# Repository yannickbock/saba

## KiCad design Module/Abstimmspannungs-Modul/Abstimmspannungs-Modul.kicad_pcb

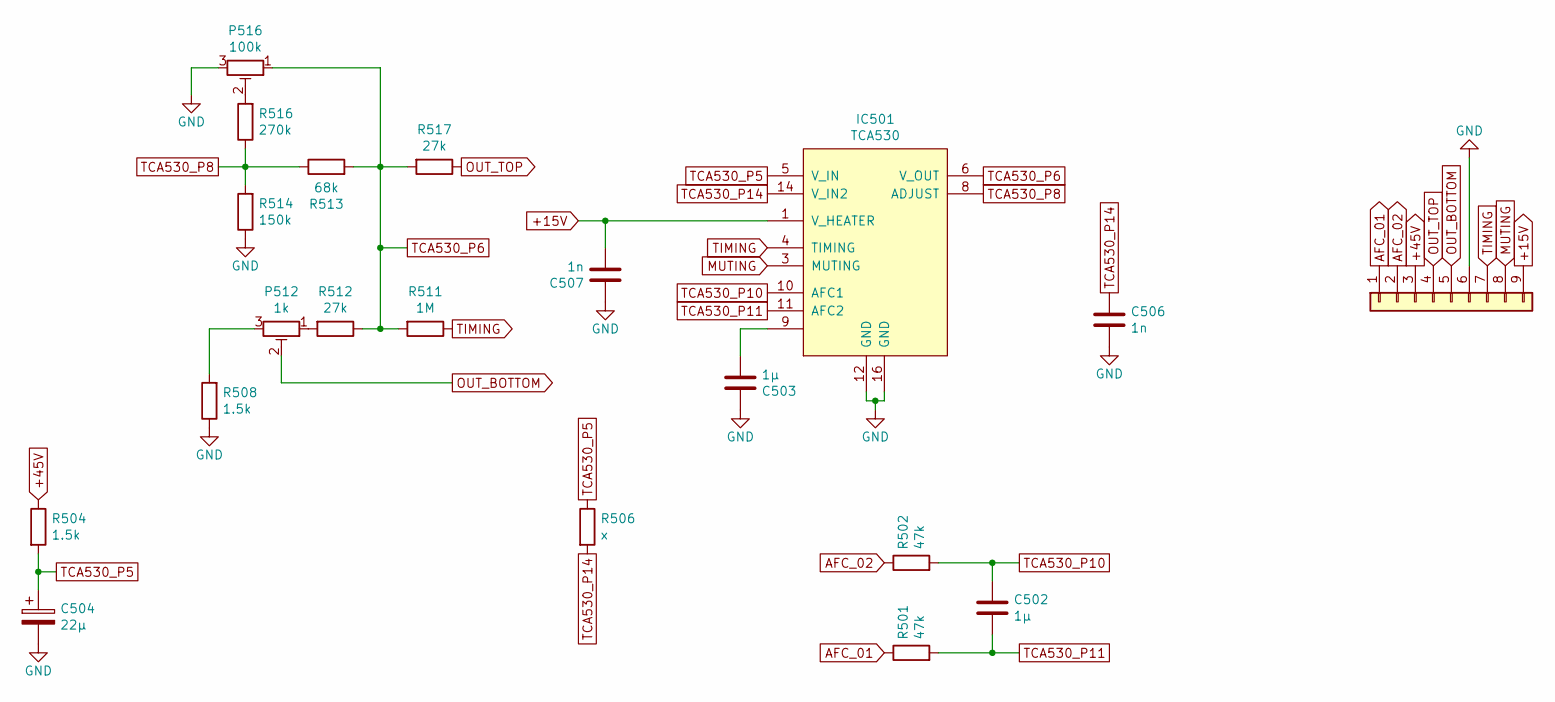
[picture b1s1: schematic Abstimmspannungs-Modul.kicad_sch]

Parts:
C502, C503: 1µ; C_Rect_L4.6mm_W5.5mm_P2.50mm_MKS02_FKP02
C504: 22µ; CP_Radial_D5.0mm_P2.00mm
C506, C507: 1n; C_Disc_D4.3mm_W1.9mm_P5.00mm
IC501: TCA530; DIP-16_W7.62mm
J1: Conn_01x09; Connector_01x09_5mm
P512: 1k; Potentiometer_Piher_PT-15-H05_Horizontal
P516: 100k; Potentiometer_Piher_PT-15-H05_Horizontal
R501, R502: 47k; R_Axial_DIN0207_L6.3mm_D2.5mm_P10.16mm_Horizontal
R504, R508: 1.5k; R_Axial_DIN0207_L6.3mm_D2.5mm_P10.16mm_Horizontal
R506: x; R_Axial_DIN0207_L6.3mm_D2.5mm_P10.16mm_Horizontal
R511: 1M; R_Axial_DIN0207_L6.3mm_D2.5mm_P10.16mm_Horizontal
R512, R517: 27k; R_Axial_DIN0207_L6.3mm_D2.5mm_P10.16mm_Horizontal
R513: 68k; R_Axial_DIN0207_L6.3mm_D2.5mm_P10.16mm_Horizontal
R514: 150k; R_Axial_DIN0207_L6.3mm_D2.5mm_P10.16mm_Horizontal
R516: 270k; R_Axial_DIN0207_L6.3mm_D2.5mm_P10.16mm_Horizontal

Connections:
+15V: C507.1, IC501.1 (V_HEATER), J1.9
+45V: J1.3, R504.1
AFC_01: J1.1, R501.1
AFC_02: J1.2, R502.1
GND: C503.2, C504.2, C506.1, C507.2, IC501.12 (GND), IC501.16 (GND), J1.6, P516.3, R508.1, R514.1
MUTING: IC501.3 (MUTING), J1.8
unnamed: C503.1, IC501.9
unnamed: P512.1, R512.2
unnamed: P512.3, R508.2
unnamed: P516.2, R516.2
OUT_BOTTOM: J1.5, P512.2
OUT_TOP: J1.4, R517.1
TCA530_P5: C504.1, IC501.5 (V_IN), R504.2, R506.1
TCA530_P6: IC501.6 (V_OUT), P516.1, R511.2, R512.1, R513.2, R517.2
TCA530_P8: IC501.8 (ADJUST), R513.1, R514.2, R516.1
TCA530_P10: C502.2, IC501.10 (AFC1), R502.2
TCA530_P11: C502.1, IC501.11 (AFC2), R501.2
TCA530_P14: C506.2, IC501.14 (V_IN2), R506.2
TIMING: IC501.4 (TIMING), J1.7, R511.1

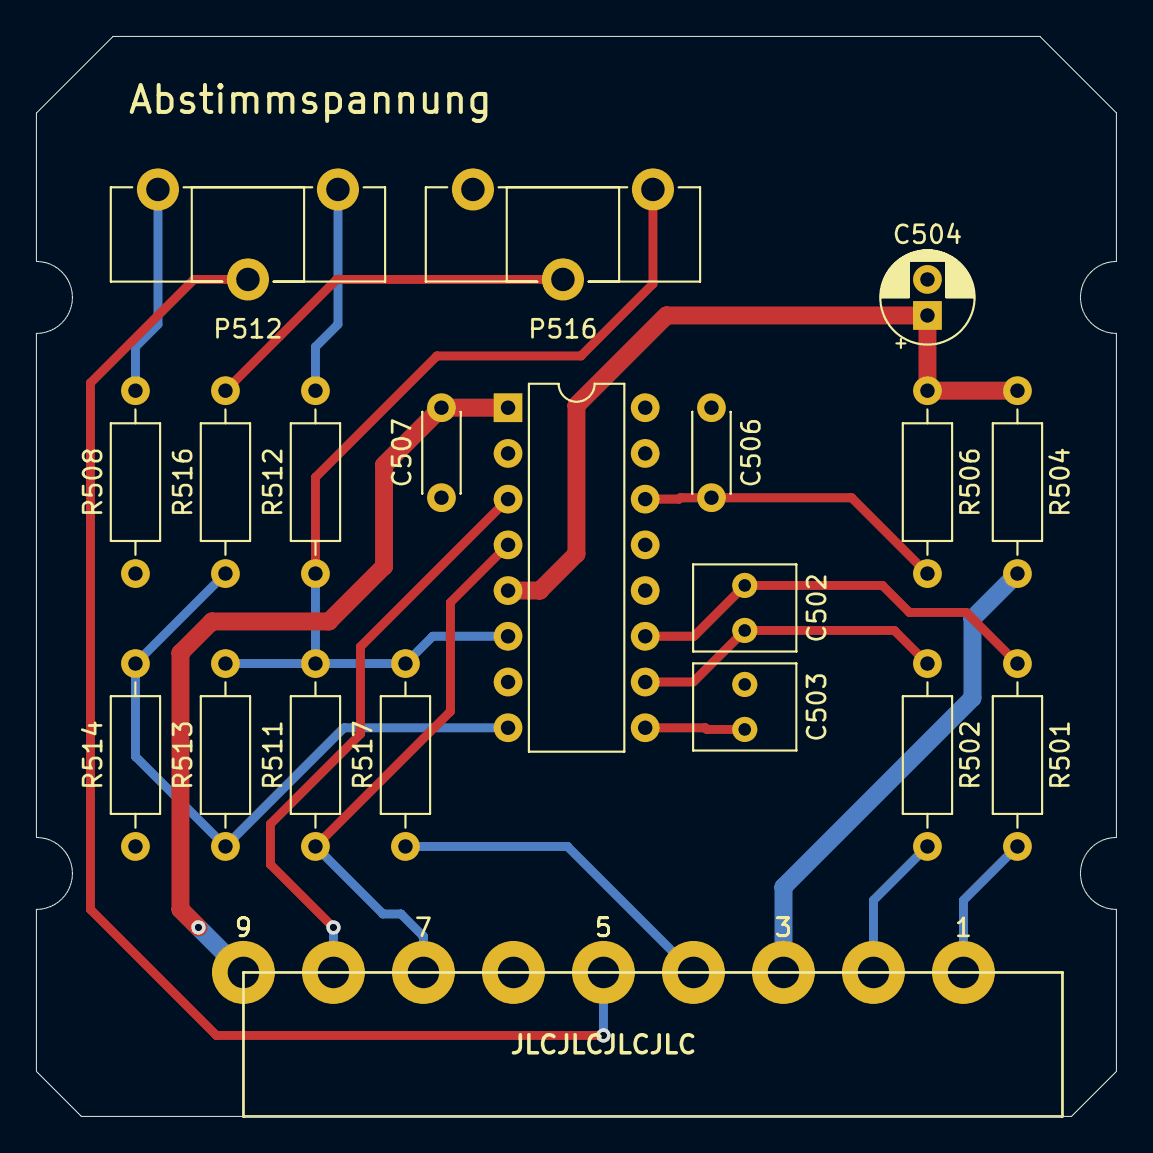
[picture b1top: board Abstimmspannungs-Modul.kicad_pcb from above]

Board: 2 copper layers, 60.0 x 60.0 mm, 20 parts (0 on the bottom side), 19 nets.

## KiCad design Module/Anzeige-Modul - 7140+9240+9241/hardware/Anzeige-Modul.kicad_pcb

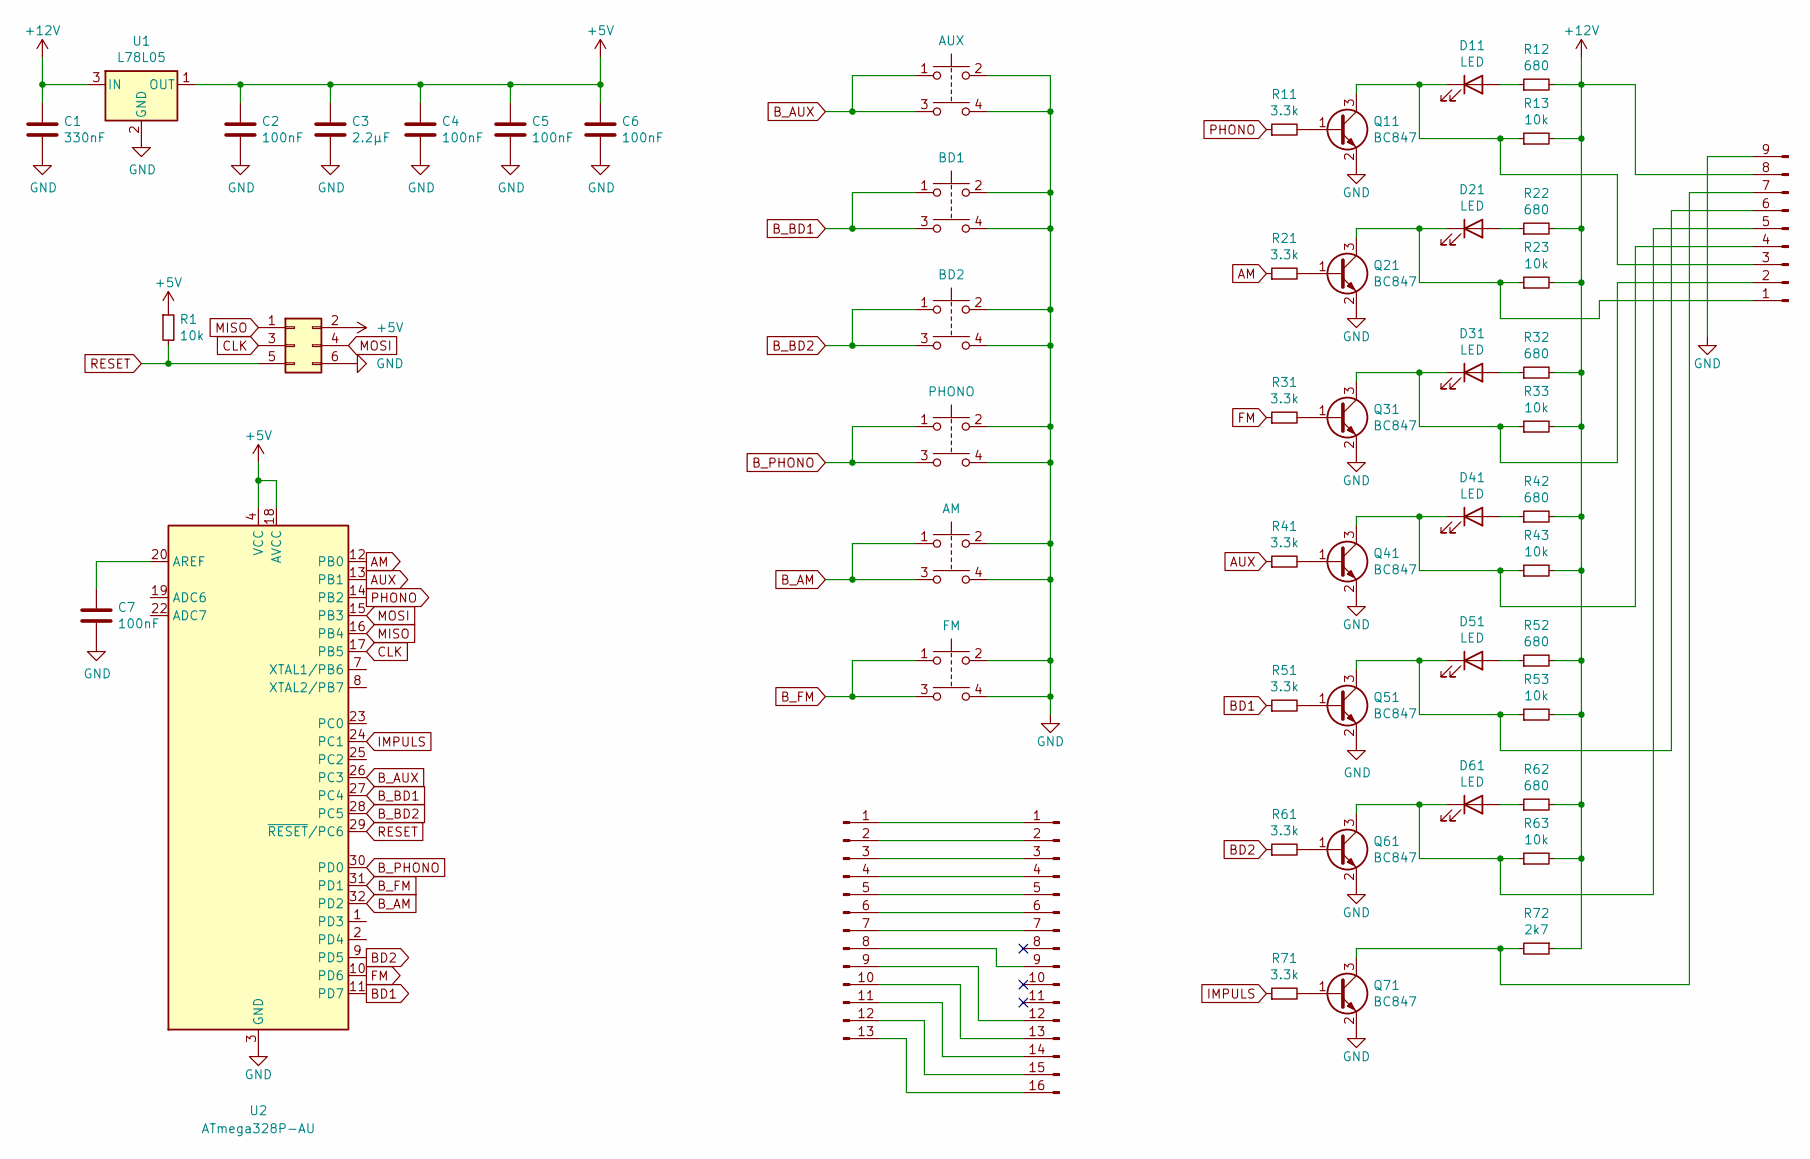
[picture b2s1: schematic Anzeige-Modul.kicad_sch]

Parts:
C1: 330nF; C_0805_2012Metric; LCSC C1740
C2, C4, C5, C6, C7: 100nF; C_0805_2012Metric; LCSC C49678
C3: 2.2µF; C_0805_2012Metric; LCSC C49217
D11, D21, D31, D41, D51, D61: LED; LED_Rectangular_W5.0mm_H2.0mm
J1: Conn_01x09_Male; PadArray_3.81mm_01x09
J3: Conn_02x03_Counter_Clockwise; PinHeader_2x03_P2.54mm_Vertical
J5: Conn_01x13_Male; PadArray_2.54mm_01x13
J6: Conn_01x16_Male; Pad_Array_2,54mm_16
Q11, Q21, Q31, Q41, Q51, Q61, Q71: BC847; SOT-23; LCSC C2146
R1, R13, R23, R33, R43, R53, R63: 10k; R_0805_2012Metric; LCSC C17414
R11, R21, R31, R41, R51, R61, R71: 3.3k; R_0805_2012Metric; LCSC C26010
R12, R22, R32, R42, R52: 680; R_0805_2012Metric; LCSC C17798
R62: 680; R_0805; LCSC C17798
R72: 2k7; R_0805_2012Metric; LCSC C17530
SW1: AUX; SW_PUSH_DPDT
SW2: BD1; SW_PUSH_DPDT
SW3: BD2; SW_PUSH_DPDT
SW4: PHONO; SW_PUSH_DPDT
SW5: AM; SW_PUSH_DPDT
SW6: FM; SW_PUSH_DPDT
U1: L78L05; SOT-89-3; LCSC C71136
U2: ATmega328P-AU; TQFP-32_7x7mm_P0.8mm; LCSC C14877

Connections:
+5V: C2.2, C3.2, C4.2, C5.2, C6.2, J3.2, R1.1, U1.1 (OUT), U2.4 (VCC), U2.6 (VCC), U2.18 (AVCC)
+12V: C1.2, J1.8, R12.2, R13.2, R22.2, R23.2, R32.2, R33.2, R42.2, R43.2, R52.2, R53.2, R62.2, R63.2, R72.1, U1.3 (IN)
AM: R21.1, U2.12 (PB0)
AUX: R41.1, U2.13 (PB1)
BD1: R51.1, U2.11 (PD7)
BD2: R61.1, U2.9 (PD5)
B_AM: SW5.1, SW5.3, U2.32 (PD2)
B_AUX: SW1.1, SW1.3, U2.26 (PC3)
B_BD1: SW2.1, SW2.3, U2.27 (PC4)
B_BD2: SW3.1, SW3.3, U2.28 (PC5)
B_FM: SW6.1, SW6.3, U2.31 (PD1)
B_PHONO: SW4.1, SW4.3, U2.30 (PD0)
CLK: J3.3, U2.17 (PB5)
FM: R31.1, U2.10 (PD6)
GND: C1.1, C2.1, C3.1, C4.1, C5.1, C6.1, C7.2, J1.9, J3.6, Q11.2 (E), Q21.2 (E), Q31.2 (E), Q41.2 (E), Q51.2 (E), Q61.2 (E), Q71.2 (E), SW1.2, SW1.4, SW2.2, SW2.4, SW3.2, SW3.4, SW4.2, SW4.4, SW5.2, SW5.4, SW6.2, SW6.4, U1.2 (GND), U2.3 (GND), U2.5 (GND), U2.21 (GND)
IMPULS: R71.1, U2.24 (PC1)
MISO: J3.1, U2.16 (PB4)
MOSI: J3.4, U2.15 (PB3)
unnamed: C7.1, U2.20 (AREF)
unnamed: D11.1 (K), J1.3, Q11.3 (C), R13.1
unnamed: D11.2 (A), R12.1
unnamed: D21.1 (K), J1.1, Q21.3 (C), R23.1
unnamed: D21.2 (A), R22.1
unnamed: D31.1 (K), J1.2, Q31.3 (C), R33.1
unnamed: D31.2 (A), R32.1
unnamed: D41.1 (K), J1.4, Q41.3 (C), R43.1
unnamed: D41.2 (A), R42.1
unnamed: D51.1 (K), J1.6, Q51.3 (C), R53.1
unnamed: D51.2 (A), R52.1
unnamed: D61.1 (K), J1.5, Q61.3 (C), R63.1
unnamed: D61.2 (A), R62.1
unnamed: J1.7, Q71.3 (C), R72.2
unnamed: J5.1, J6.1
unnamed: J5.2, J6.2
unnamed: J5.3, J6.3
unnamed: J5.4, J6.4
unnamed: J5.5, J6.5
unnamed: J5.6, J6.6
unnamed: J5.7, J6.7
unnamed: J5.8, J6.9
unnamed: J5.9, J6.12
unnamed: J5.10, J6.13
unnamed: J5.11, J6.14
unnamed: J5.12, J6.15
unnamed: J5.13, J6.16
unnamed: Q11.1 (B), R11.2
unnamed: Q21.1 (B), R21.2
unnamed: Q31.1 (B), R31.2
unnamed: Q41.1 (B), R41.2
unnamed: Q51.1 (B), R51.2
unnamed: Q61.1 (B), R61.2
unnamed: Q71.1 (B), R71.2
PHONO: R11.1, U2.14 (PB2)
RESET: J3.5, R1.2, U2.29 (~RESET/PC6)

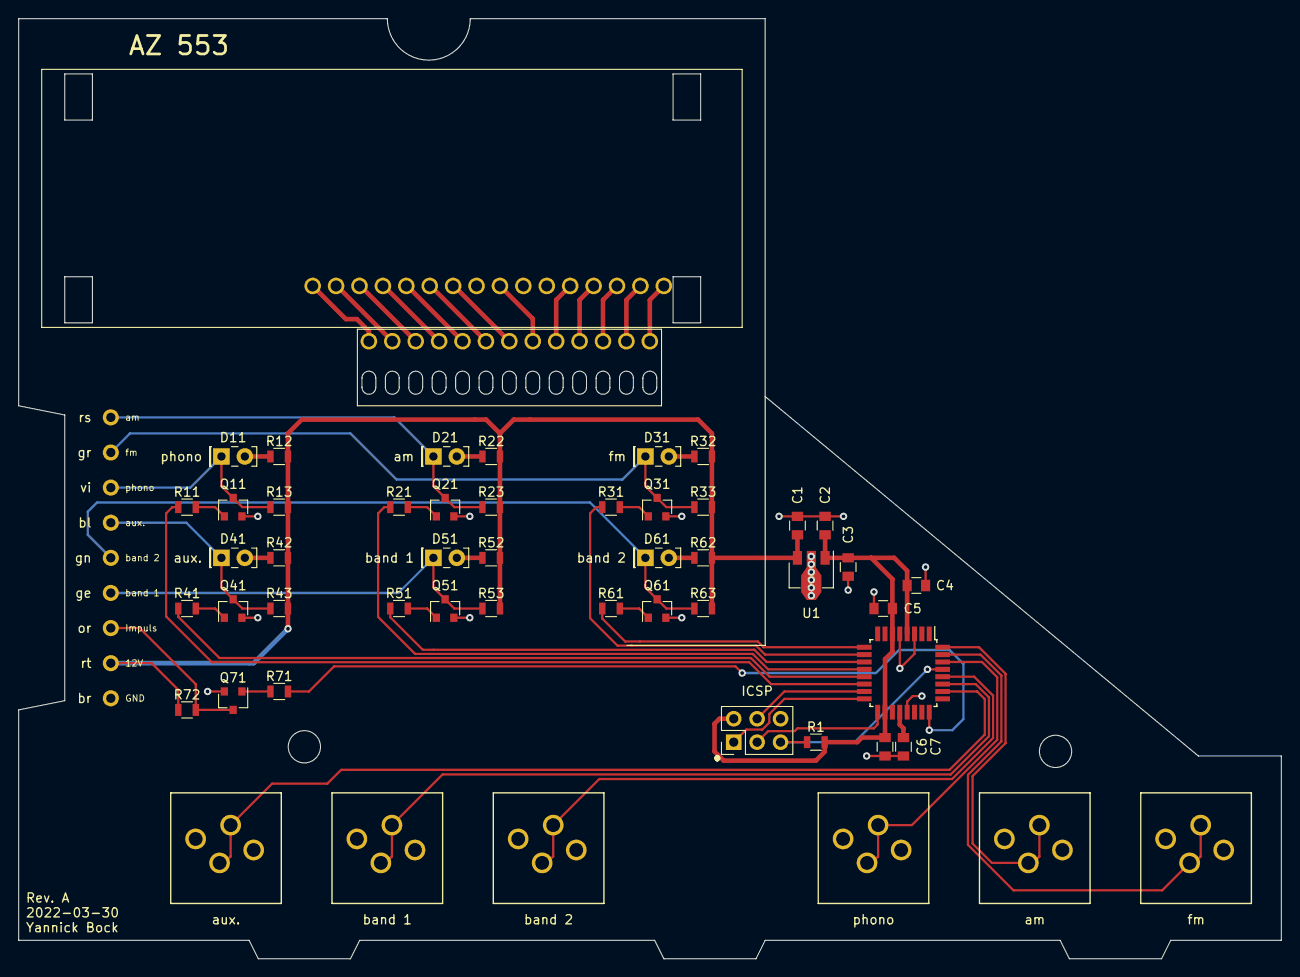
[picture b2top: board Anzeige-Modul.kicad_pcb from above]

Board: 2 copper layers, 137.0 x 102.0 mm, 53 parts (0 on the bottom side), 54 nets.

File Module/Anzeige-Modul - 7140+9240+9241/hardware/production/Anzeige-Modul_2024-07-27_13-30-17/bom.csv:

Designator,Footprint,Quantity,Value,LCSC Part #
C1,0805,1,330n,C1739
C2,0805,1,22µ,C377773
"C3, C4, C5, C6, C7",0805,5,100n, C49678
"Q11, Q21, Q31, Q41, Q51, Q61, Q71",SOT-23,7,BC847,C2146
"R1, R13, R23, R33, R43, R53, R63",0805,7,10k,C17414
"R11, R21, R31, R41, R51, R61, R71",0805,7,3.3k,C26010
"R12, R22, R32, R42, R52, R62",0805,6,680,C17798
R72,0805,1,2k7,C17530
U1,SOT-89-3,1,L78L05,C71136
U2,TQFP-32_7x7mm_P0.8mm,1,ATmega328P-AU,C14877

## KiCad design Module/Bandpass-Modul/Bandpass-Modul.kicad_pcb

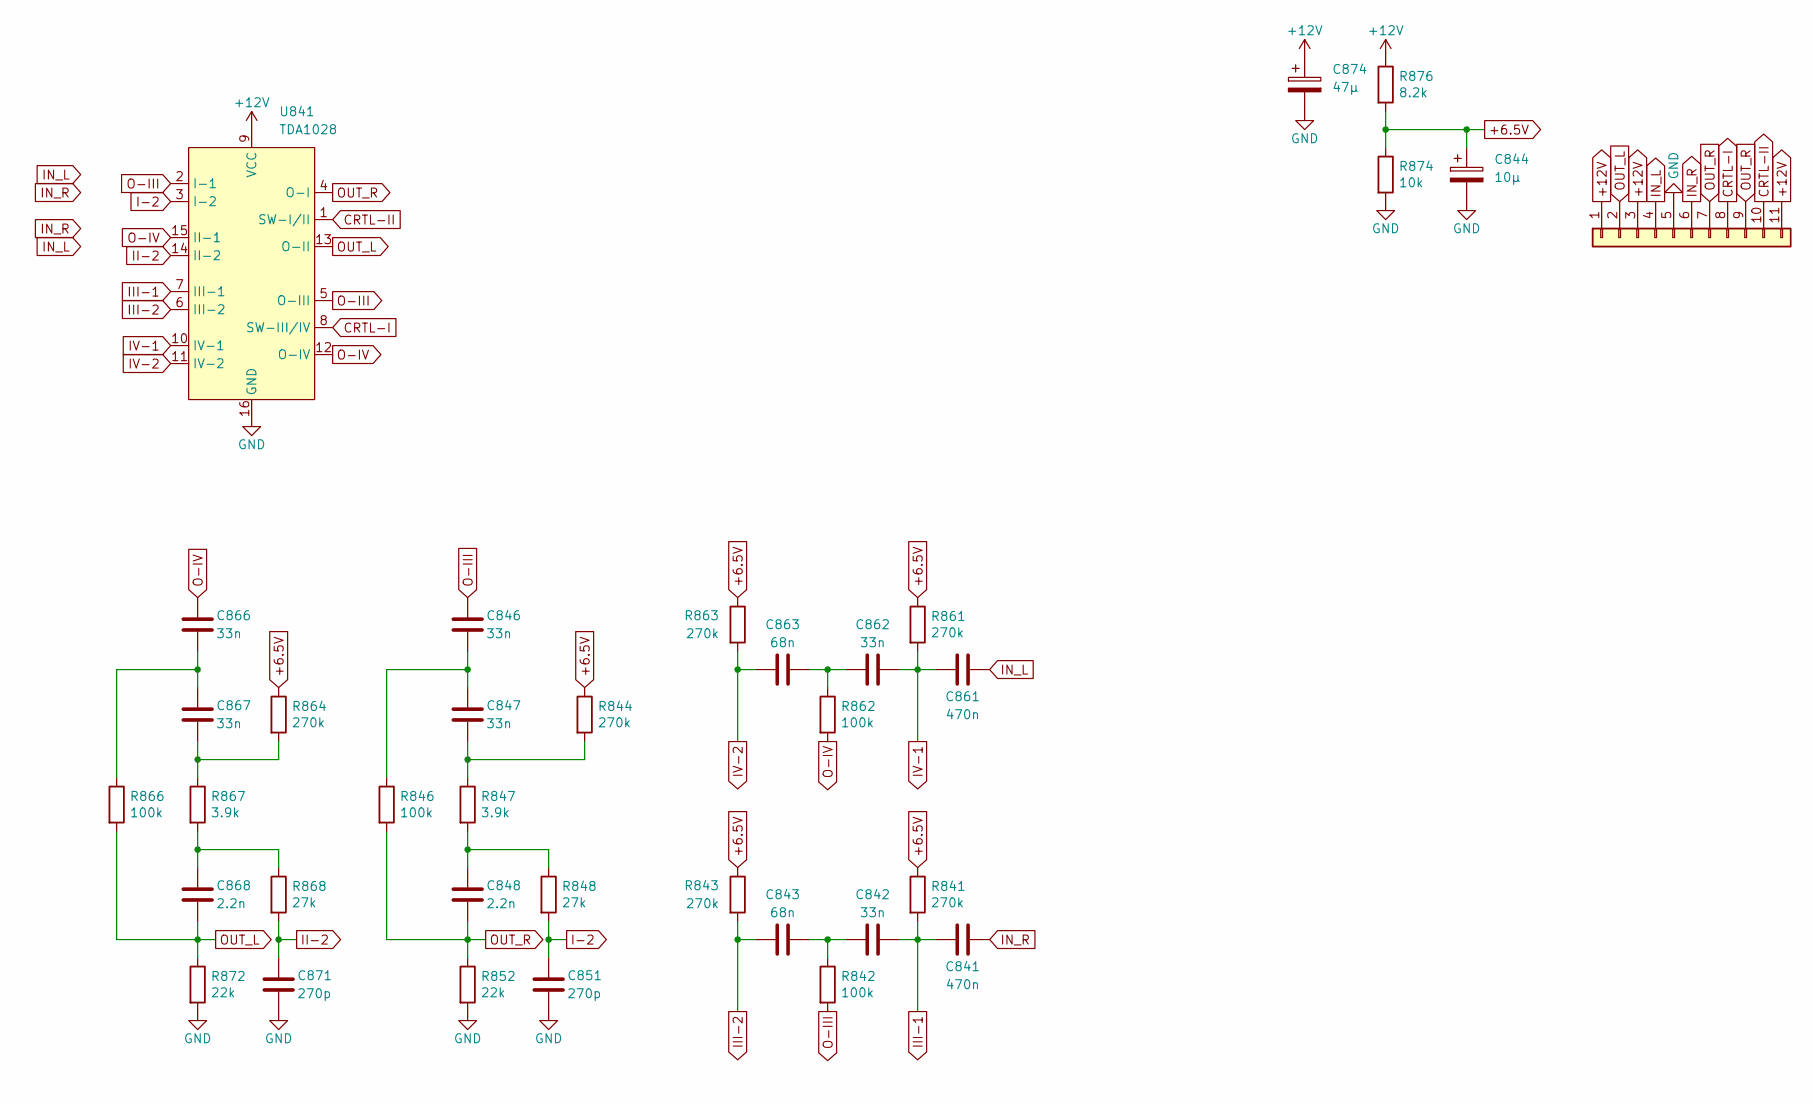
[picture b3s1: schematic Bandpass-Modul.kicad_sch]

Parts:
C841, C861: 470n; C_Rect_L10.0mm_W4.0mm_P7.50mm_MKS4
C842, C846, C847, C862, C866, C867: 33n; C_Rect_L10.0mm_W2.5mm_P7.50mm_MKS4
C843, C863: 68n; C_Rect_L10.0mm_W2.5mm_P7.50mm_MKS4
C844: 10µ; CP_Radial_D5.0mm_P2.00mm
C848, C868: 2.2n; C_Rect_L10.0mm_W4.0mm_P7.50mm_MKS4
C851, C871: 270p; C_Disc_D6.0mm_W2.5mm_P5.00mm
C874: 47µ; CP_Radial_D6.3mm_P2.50mm
J1: Conn_01x13; Connector_01x11_5mm
R841, R843, R844, R861, R863, R864: 270k; R_Axial_DIN0207_L6.3mm_D2.5mm_P10.16mm_Horizontal
R842, R846, R862, R866: 100k; R_Axial_DIN0207_L6.3mm_D2.5mm_P10.16mm_Horizontal
R847, R867: 3.9k; R_Axial_DIN0207_L6.3mm_D2.5mm_P10.16mm_Horizontal
R848, R868: 27k; R_Axial_DIN0207_L6.3mm_D2.5mm_P10.16mm_Horizontal
R852, R872: 22k; R_Axial_DIN0207_L6.3mm_D2.5mm_P10.16mm_Horizontal
R874: 10k; R_Axial_DIN0207_L6.3mm_D2.5mm_P10.16mm_Horizontal
R876: 8.2k; R_Axial_DIN0207_L6.3mm_D2.5mm_P10.16mm_Horizontal
U841: TDA1028; DIP-16_W7.62mm

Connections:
+6.5V: C844.1, R841.1, R843.1, R844.1, R861.1, R863.1, R864.1, R874.1, R876.2
+12V: C874.1, J1.1, J1.3, J1.11, R876.1, U841.9 (VCC)
CRTL-I: J1.8, U841.8 (SW-III/IV)
CRTL-II: J1.10, U841.1 (SW-I/II)
GND: C844.2, C851.2, C871.2, C874.2, J1.5, R852.2, R872.2, R874.2, U841.16 (GND)
I-2: C851.1, R848.2, U841.3 (I-2)
II-2: C871.1, R868.2, U841.14 (II-2)
III-1: C841.1, C842.2, R841.2, U841.7 (III-1)
III-2: C843.2, R843.2, U841.6 (III-2)
IN_L: C861.2, J1.4
IN_R: C841.2, J1.6
IV-1: C861.1, C862.2, R861.2, U841.10 (IV-1)
IV-2: C863.2, R863.2, U841.11 (IV-2)
unnamed: C842.1, C843.1, R842.1
unnamed: C846.2, C847.1, R846.1
unnamed: C847.2, R844.2, R847.1
unnamed: C848.1, R847.2, R848.1
unnamed: C862.1, C863.1, R862.1
unnamed: C866.2, C867.1, R866.1
unnamed: C867.2, R864.2, R867.1
unnamed: C868.1, R867.2, R868.1
O-III: C846.1, R842.2, U841.2 (I-1), U841.5 (O-III)
O-IV: C866.1, R862.2, U841.12 (O-IV), U841.15 (II-1)
OUT_L: C868.2, J1.2, R866.2, R872.1, U841.13 (O-II)
OUT_R: C848.2, J1.7, J1.9, R846.2, R852.1, U841.4 (O-I)

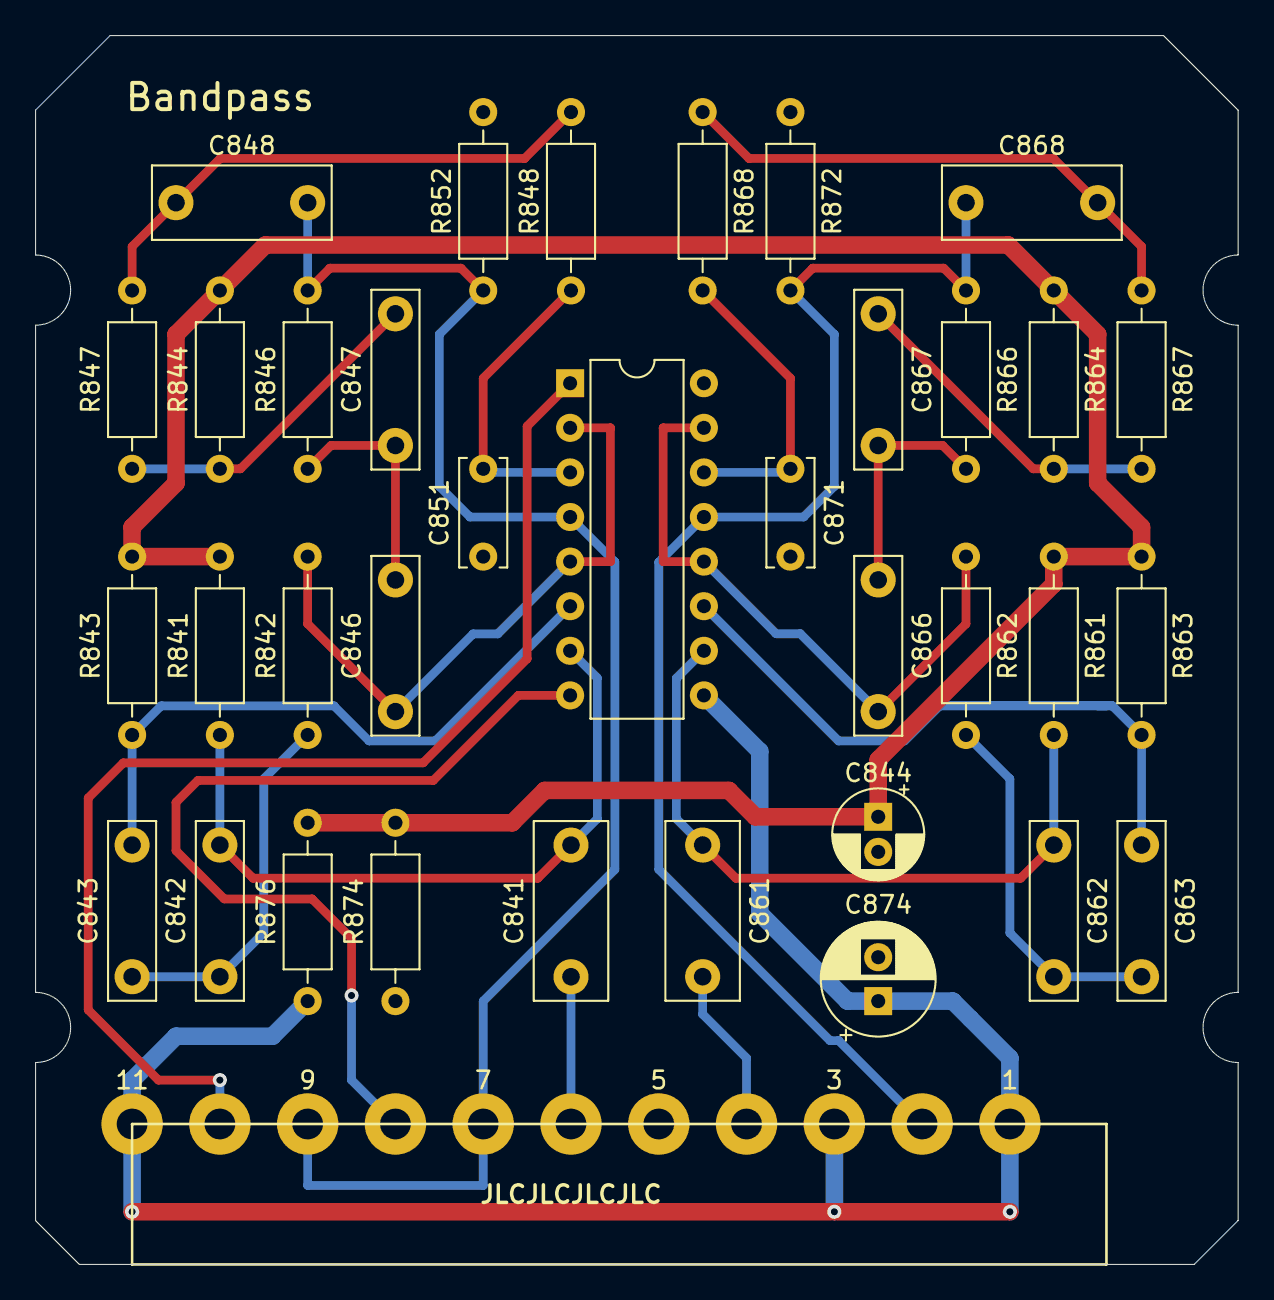
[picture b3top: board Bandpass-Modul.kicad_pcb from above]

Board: 2 copper layers, 68.5 x 70.0 mm, 36 parts (0 on the bottom side), 25 nets.

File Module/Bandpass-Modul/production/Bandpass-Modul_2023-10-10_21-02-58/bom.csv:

Designator,Footprint,Quantity,Value,LCSC Part #
"C841, C861",C_Rect_L10.0mm_W4.0mm_P7.50mm_MKS4,2,470n,
"C842, C846, C847, C862, C866, C867",C_Rect_L10.0mm_W2.5mm_P7.50mm_MKS4,6,33n,
"C843, C863",C_Rect_L10.0mm_W2.5mm_P7.50mm_MKS4,2,68n,
C844,CP_Radial_D5.0mm_P2.00mm,1,10µ,
"C848, C868",C_Rect_L10.0mm_W4.0mm_P7.50mm_MKS4,2,2.2n,
"C851, C871",C_Disc_D6.0mm_W2.5mm_P5.00mm,2,270p,
C874,CP_Radial_D6.3mm_P2.50mm,1,47µ,
J1,Connector_01x11_5mm,1,Conn_01x13,
"R841, R861",R_Axial_DIN0207_L6.3mm_D2.5mm_P10.16mm_Horizontal,2,270k,
"R842, R846, R862, R866",R_Axial_DIN0207_L6.3mm_D2.5mm_P10.16mm_Horizontal,4,100k,
"R843, R844, R863, R864",R_Axial_DIN0207_L6.3mm_D2.5mm_P10.16mm_Horizontal,4,270k,
"R847, R867",R_Axial_DIN0207_L6.3mm_D2.5mm_P10.16mm_Horizontal,2,3.9k,
"R848, R868",R_Axial_DIN0207_L6.3mm_D2.5mm_P10.16mm_Horizontal,2,27k,
"R852, R872",R_Axial_DIN0207_L6.3mm_D2.5mm_P10.16mm_Horizontal,2,22k,
R874,R_Axial_DIN0207_L6.3mm_D2.5mm_P10.16mm_Horizontal,1,10k,
R876,R_Axial_DIN0207_L6.3mm_D2.5mm_P10.16mm_Horizontal,1,8.2k,
U841,DIP-16_W7.62mm,1,TDA1028,

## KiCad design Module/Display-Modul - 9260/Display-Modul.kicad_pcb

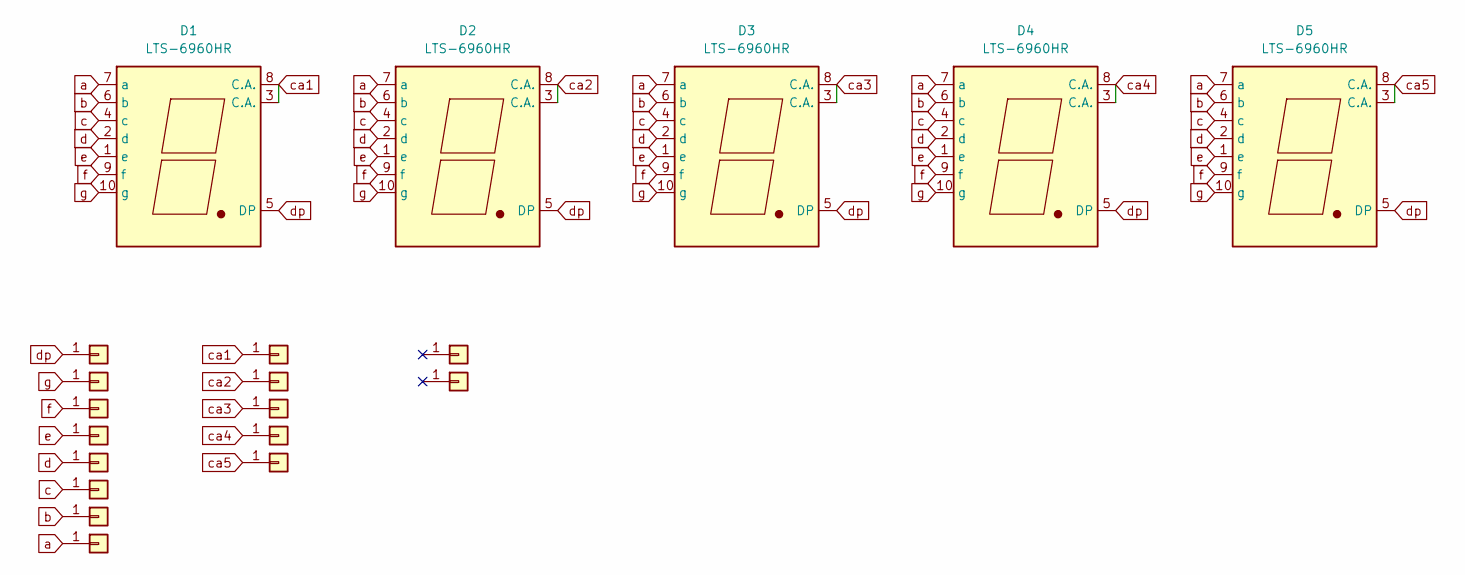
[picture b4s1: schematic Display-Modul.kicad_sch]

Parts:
D1, D2, D3, D4, D5: LTS-6960HR; 7SegmentLED_LTS6760_LTS6780
J1, J2, J3, J4, J5, J6, J7, J8, J9, J10, J11, J12, J13, J14, J15: Conn_01x01; Solder-Pad

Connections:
a: D1.7 (a), D2.7 (a), D3.7 (a), D4.7 (a), D5.7 (a), J8.1
b: D1.6 (b), D2.6 (b), D3.6 (b), D4.6 (b), D5.6 (b), J7.1
c: D1.4 (c), D2.4 (c), D3.4 (c), D4.4 (c), D5.4 (c), J6.1
ca1: D1.3 (C.A.), D1.8 (C.A.), J9.1
ca2: D2.3 (C.A.), D2.8 (C.A.), J10.1
ca3: D3.3 (C.A.), D3.8 (C.A.), J11.1
ca4: D4.3 (C.A.), D4.8 (C.A.), J12.1
ca5: D5.3 (C.A.), D5.8 (C.A.), J13.1
d: D1.2 (d), D2.2 (d), D3.2 (d), D4.2 (d), D5.2 (d), J5.1
dp: D1.5 (DP), D2.5 (DP), D3.5 (DP), D4.5 (DP), D5.5 (DP), J1.1
e: D1.1 (e), D2.1 (e), D3.1 (e), D4.1 (e), D5.1 (e), J4.1
f: D1.9 (f), D2.9 (f), D3.9 (f), D4.9 (f), D5.9 (f), J3.1
g: D1.10 (g), D2.10 (g), D3.10 (g), D4.10 (g), D5.10 (g), J2.1

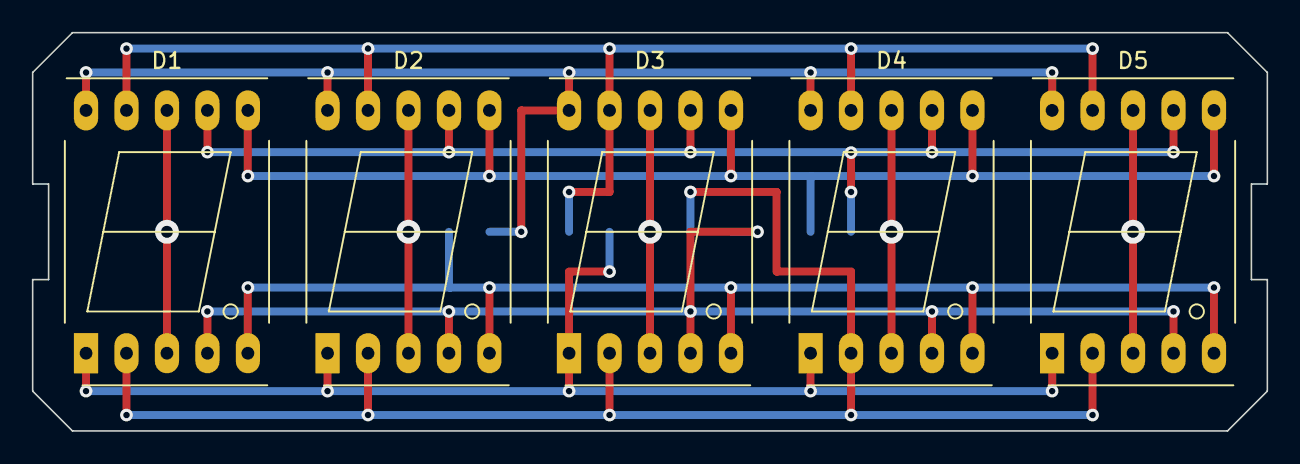
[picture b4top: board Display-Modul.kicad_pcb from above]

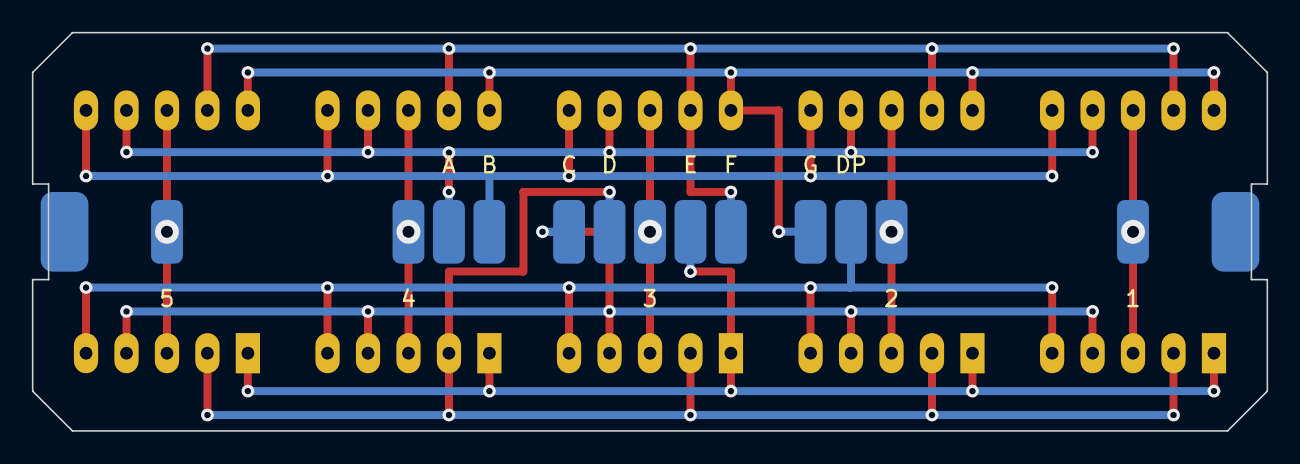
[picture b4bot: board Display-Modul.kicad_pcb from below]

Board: 2 copper layers, 77.5 x 25.0 mm, 20 parts (15 on the bottom side), 13 nets.

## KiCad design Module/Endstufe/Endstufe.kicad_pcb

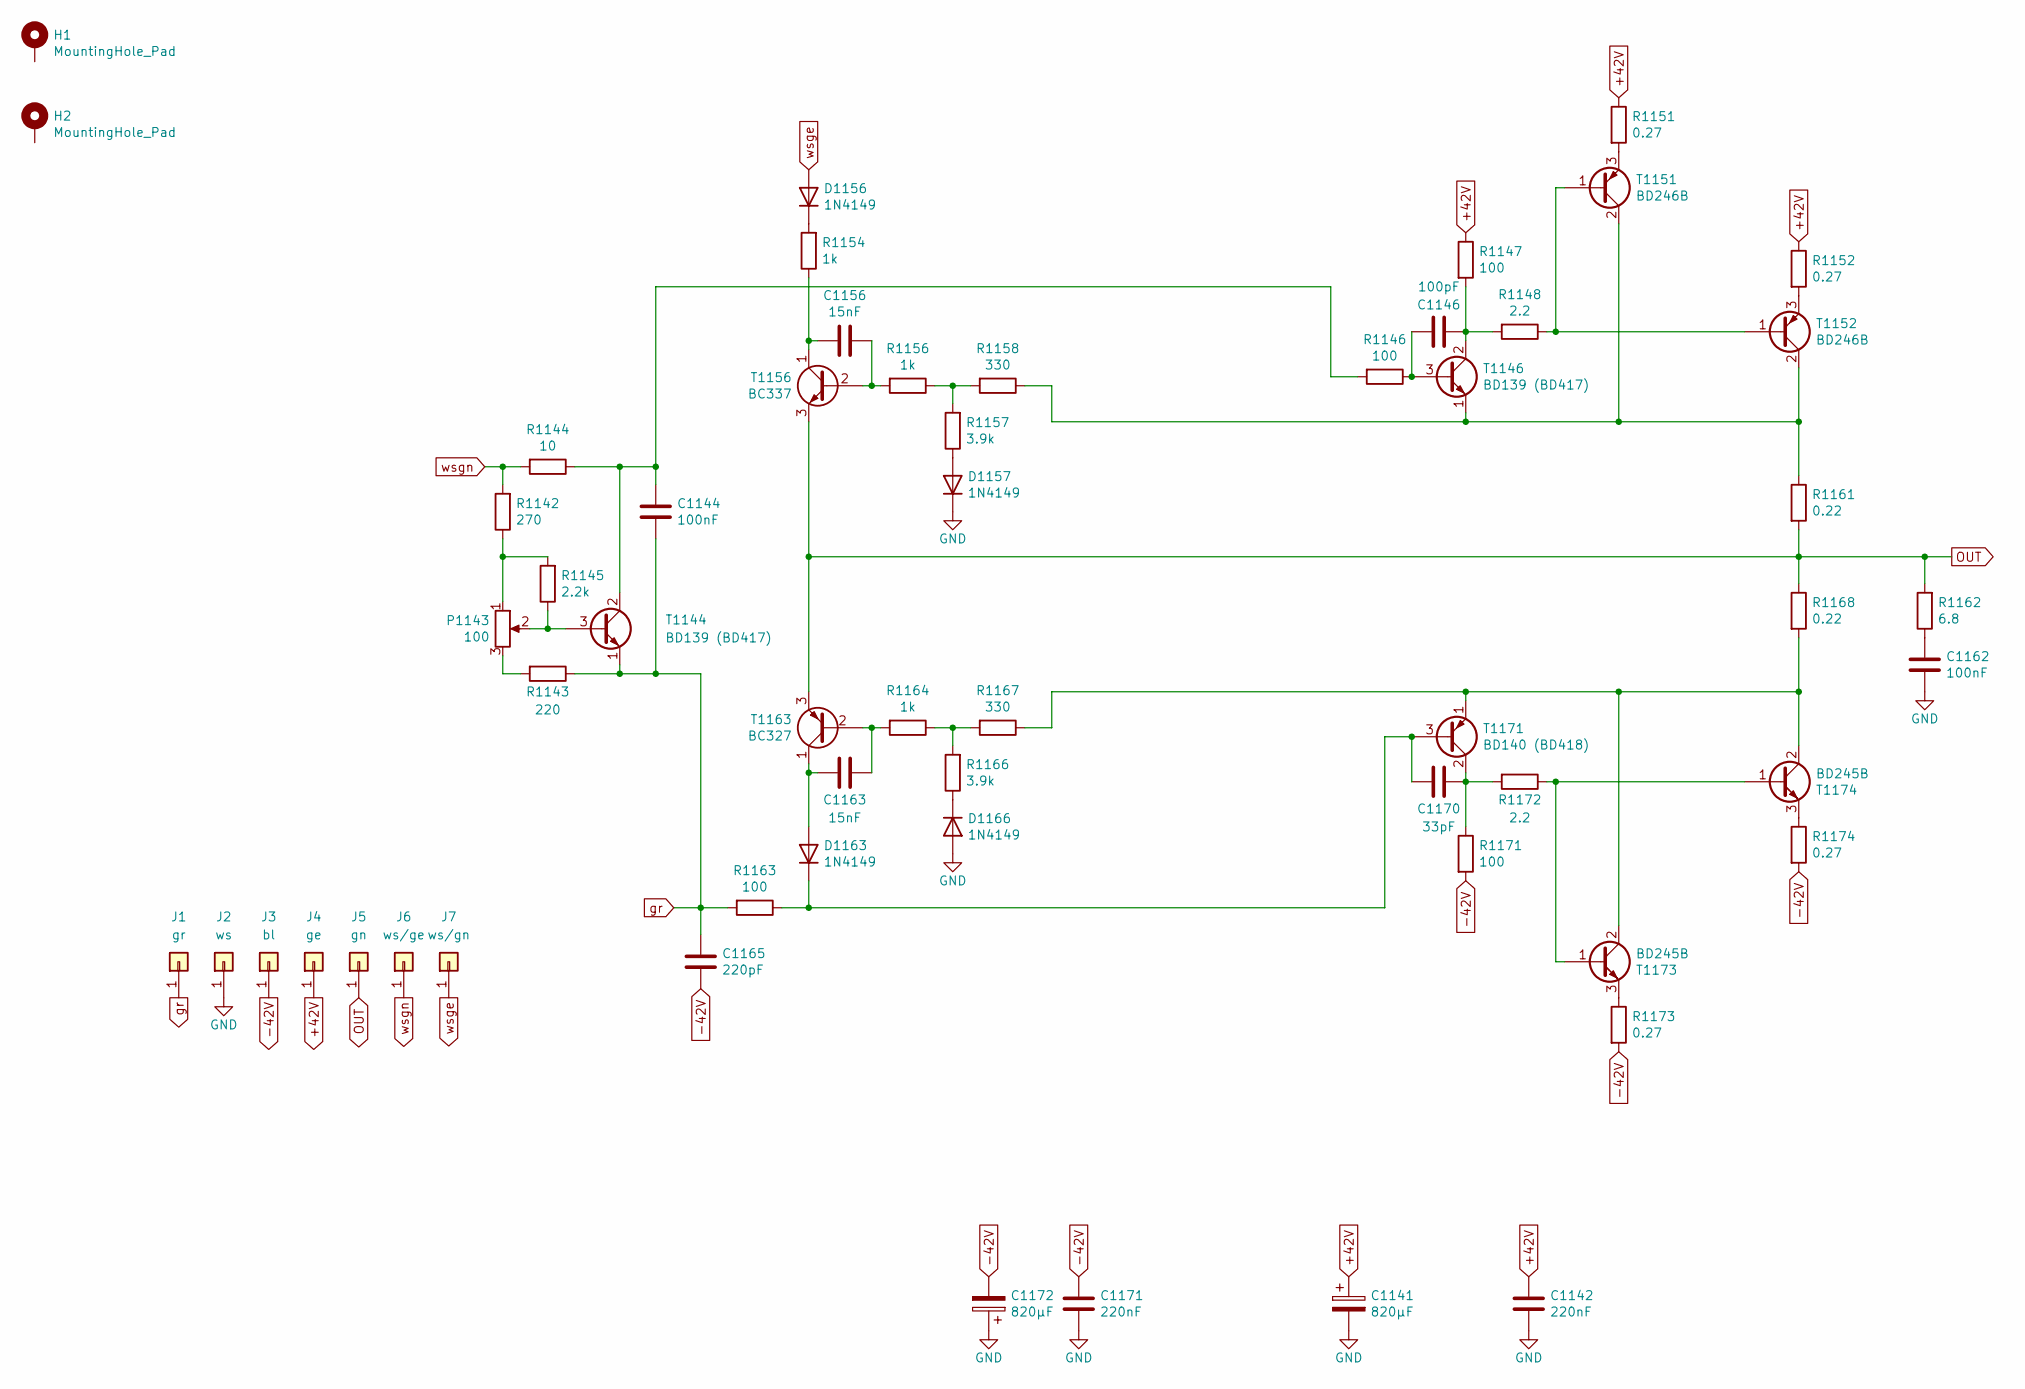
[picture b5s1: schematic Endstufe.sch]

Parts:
C1141, C1172: 820µF; CP_Radial_D16.0mm_P7.50mm
C1142, C1171: 220nF; C_Rect_L7.2mm_W3.0mm_P5.00mm_FKS2_FKP2_MKS2_MKP2
C1144, C1162: 100nF; C_Rect_L7.2mm_W2.5mm_P5.00mm_FKS2_FKP2_MKS2_MKP2
C1146: 100pF; C_Disc_D5.0mm_W2.5mm_P5.00mm
C1156, C1163: 15nF; C_Disc_D5.0mm_W2.5mm_P5.00mm
C1165: 220pF; C_Disc_D5.0mm_W2.5mm_P5.00mm
C1170: 33pF; C_Disc_D5.0mm_W2.5mm_P5.00mm
D1156, D1157, D1163, D1166: 1N4149; D_DO-35_SOD27_P10.16mm_Horizontal
H1, H2: MountingHole_Pad; MountingHole_3.7mm_Pad
J1: gr; SolderWirePad_single_2mmDrill
J2: ws; SolderWirePad_single_2mmDrill
J3: bl; SolderWirePad_single_2mmDrill
J4: ge; SolderWirePad_single_2mmDrill
J5: gn; SolderWirePad_single_2mmDrill
J6: ws/ge; SolderWirePad_single_2mmDrill
J7: ws/gn; SolderWirePad_single_2mmDrill
P1143: 100; Potentiometer_Trimmer_Piher_PT-10v10_Horizontal_Px10.0mm_Py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
R1142: 270; R_Axial_DIN0207_L6.3mm_D2.5mm_P10.16mm_Horizontal
R1143: 220; R_Axial_DIN0207_L6.3mm_D2.5mm_P10.16mm_Horizontal
R1144: 10; R_Axial_DIN0207_L6.3mm_D2.5mm_P10.16mm_Horizontal
R1145: 2.2k; R_Axial_DIN0207_L6.3mm_D2.5mm_P10.16mm_Horizontal
R1146, R1147, R1163, R1171: 100; R_Axial_DIN0207_L6.3mm_D2.5mm_P10.16mm_Horizontal
R1148, R1172: 2.2; R_Axial_DIN0207_L6.3mm_D2.5mm_P10.16mm_Horizontal
R1151, R1152, R1173, R1174: 0.27; R_Axial_DIN0414_L11.9mm_D4.5mm_P15.24mm_Horizontal
R1154, R1156, R1164: 1k; R_Axial_DIN0207_L6.3mm_D2.5mm_P10.16mm_Horizontal
R1157, R1166: 3.9k; R_Axial_DIN0207_L6.3mm_D2.5mm_P10.16mm_Horizontal
R1158, R1167: 330; R_Axial_DIN0207_L6.3mm_D2.5mm_P10.16mm_Horizontal
R1161, R1168: 0.22; R_Axial_DIN0414_L11.9mm_D4.5mm_P20.32mm_Horizontal
R1162: 6.8; R_Axial_DIN0411_L9.9mm_D3.6mm_P15.24mm_Horizontal
T1144, T1146: BD139 (BD417); TO-126_Vertical
T1151, T1152: BD246B; TO-247_TO-3P_Vertical
T1156: BC337; TO-92_Rugged
T1163: BC327; TO-92_Rugged
T1171: BD140 (BD418); TO-126_Vertical
T1173, T1174: BD245B; TO-247_TO-3P_Vertical

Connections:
+42V: C1141.1, C1142.1, J4.1, R1147.1, R1151.1, R1152.1
-42V: C1165.2, C1171.1, C1172.2, J3.1, R1171.2, R1173.2, R1174.2
GND: C1141.2, C1142.2, C1162.2, C1171.2, C1172.1, D1157.1 (K), D1166.2 (A), J2.1
unnamed: C1144.1, R1144.1, R1146.2, T1144.2 (C)
unnamed: C1146.1, R1146.1, T1146.3 (B)
unnamed: C1146.2, R1147.2, R1148.2, T1146.2 (C)
unnamed: C1156.1, R1156.2, T1156.2 (B)
unnamed: C1156.2, R1154.1, T1156.1 (C)
unnamed: C1162.1, R1162.1
unnamed: C1163.1, R1164.2, T1163.2 (B)
unnamed: C1163.2, D1163.2 (A), T1163.1 (C)
unnamed: C1170.1, R1171.1, R1172.2, T1171.2 (C)
unnamed: C1170.2, D1163.1 (K), R1163.1, T1171.3 (B)
unnamed: D1156.1 (K), R1154.2
unnamed: D1157.2 (A), R1157.1
unnamed: D1166.1 (K), R1166.1
unnamed: P1143.1, R1142.1, R1145.2
unnamed: P1143.2, R1145.1, T1144.3 (B)
unnamed: P1143.3, R1143.2
unnamed: R1148.1, T1151.1 (B), T1152.1 (B)
unnamed: R1151.2, T1151.3 (E)
unnamed: R1152.2, T1152.3 (E)
unnamed: R1156.1, R1157.2, R1158.2
unnamed: R1158.1, R1161.1, T1146.1 (E), T1151.2 (C), T1152.2 (C)
unnamed: R1164.1, R1166.2, R1167.2
unnamed: R1167.1, R1168.2, T1171.1 (E), T1173.2 (C), T1174.2 (C)
unnamed: R1172.1, T1173.1 (B), T1174.1 (B)
unnamed: R1173.1, T1173.3 (E)
unnamed: R1174.1, T1174.3 (E)
OUT: J5.1, R1161.2, R1162.2, R1168.1, T1156.3 (E), T1163.3 (E)
gr: C1144.2, C1165.1, J1.1, R1143.1, R1163.2, T1144.1 (E)
wsge: D1156.2 (A), J7.1
wsgn: J6.1, R1142.2, R1144.2

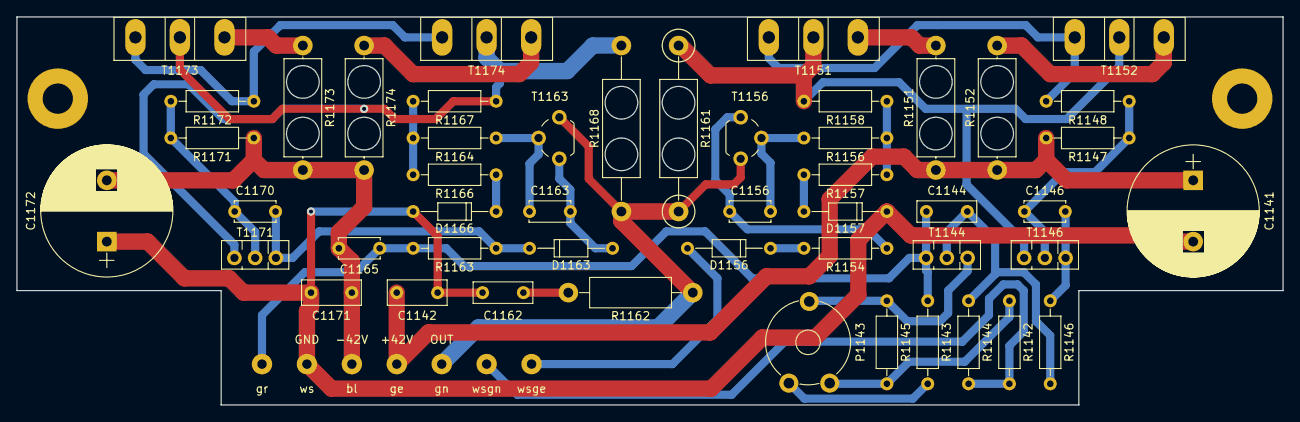
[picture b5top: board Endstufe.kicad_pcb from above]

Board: 2 copper layers, 155.0 x 47.5 mm, 58 parts (0 on the bottom side), 33 nets.
